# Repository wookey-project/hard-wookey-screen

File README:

# WooKey Screen PCB

## Introduction

Wookey | https://wookey-project.github.io/
Copyright 2018 The wookey project team <wookey@ssi.gouv.fr>

The Wookey from [ANSSI](https://www.ssi.gouv.fr) is an open source
hardware design, implementing an Encrypted Flash Drives.

This repository is aimed towards developers.

### Revision information

This directory contains the hardware design for the Wookey board, first public version (Wookey V2).

### PCB editing tools

All PCB files (schematic and PCB layout) have been designed using the KiCad EDA.
This Cross Platform and Open Source Electronics Design Automation Suite can be downloaded
on http://kicad-pcb.org/.

## Production files generation 101

### Configure the project

KiCad binaries location may change regarding your operating system.
This is why you have to set your environment.
This is done by sourcing the `setenv.sh` script. This script exports
all paths that are required in order to automaticaly generate the production files.

Most of the time, the paths proposed in this script are not the one you use in your specific installation.
The `setenv.sh` script support easy variables overloading by including a `setenv.local.sh` script file if this file exists in the same directory.
If you need to overload some of the variables of the `setenv.sh` script, just add them to your own `setenv.local.sh` file.
Here is an example to define KiCad environement path on Apple Mac OS.

```
  $ echo "export PYTHON_BIN_PATH = /Applications/KiCad/kicad.app/Contents/Frameworks/Python.framework/Versions/2.7/bin/python" > setenv.local.sh
  $ source setenv.sh
  Loading local SDK settings...
  =========================================================
  === Kicad environment configuration
  =========================================================
  PYTHON_BIN_PATH   = /Applications/KiCad/kicad.app/Contents/Frameworks/Python.framework/Versions/2.7/bin/python
  PYTHON_PATH     = /Applications/Kicad/kicad.app/Contents/Frameworks/python/site-packages
  BOM_GEN_PATH = /Applications/Kicad/kicad.app/Contents/SharedSupport/plugins/bom2grouped_csv.xsl
  TOOLS_PATH = ../../../tools
  =========================================================
```

The production files can be generated using the following command.

```
$ make
```

This will generate the production files in a new sub directory.
The directory name may differ according the project your are working with.

## PCB Pinout

## PCB Layers

### PCB TOP layer

### PCB BOTTOM layer

### Layers

Order and type of copper layers:
  TOP:  signal, front components
  GND:  ground plane
  PWR:  ground and power plane
  BOT:  signal, back components

### Stackup
4 layers, 1.6mm thickness
Outer layers 1 oz base copper foil
Inner layers 0.5 oz base copper foil

Electroless Nickel Immersion Gold (ENIG) surface finish

solder resist   0.0254mm
copper          0.0356mm    L1 (TOP)
FR408 prepreg   0.1702mm
copper          0.0178mm    L2 (GND)
FR408           1.1938mm
copper          0.0178mm    L3 (PWR)
FR408 prepreg   0.1702mm
copper          0.0356mm    L4 (BOT)
solder resist   0.0254mm

The substrate for both the core and prepreg is FR408,
with a dielectric constant of 3.66 at 1GHz.
The prepreg is comprised of 2 layers of Isola 2113.

## Regulatory compliance & handling

The Wookey board is intended for use as a development platform for hardware
or software. The board is an open system design, which does not include a
shielded enclosure. This may cause interference to other electrical or
electronic devices in close proximity. In a domestic environment, this product
may cause radio interference in which case the user may be required to take
adequate measures. In addition, this board should not be used near any medical
equipment or RF devices.

The board is sensitive to ESD. Hold the board only by its edges. After removing
the board from its box, place it on a grounded, static-free surface.

The board can become hot, like any fan-less design, during continuous high CPU
loads, mind its temperature while handling it.

## License

Wookey | https://wookey-project.github.io/
Copyright 2018 The wookey project team <wookey@ssi.gouv.fr>

This is an open hardware design licensed under the terms of the CERN Open
Hardware Licence (OHL) v1.2.

You may redistribute and modify this documentation under the terms of the CERN
OHL v.1.2 (http://ohwr.org/cernohl). This documentation is distributed WITHOUT
ANY EXPRESS OR IMPLIED WARRANTY, INCLUDING OF MERCHANTABILITY, SATISFACTORY
QUALITY AND FITNESS FOR A PARTICULAR PURPOSE. Please see the CERN OHL v.1.2 for
applicable conditions.

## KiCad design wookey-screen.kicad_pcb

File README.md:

# WooKey Screen PCB

## Introduction

Wookey | https://wookey-project.github.io/
Copyright 2018 ANSSI

Authors: The Wookey project Team <wookey@ssi.gouv.fr>

The Wookey from [ANSSI](https://www.ssi.gouv.fr) is an open source
hardware design, implementing an Encrypted Flash Drives.

This repository is aimed towards developers.

### Revision information

This directory contains the hardware design for the Wookey board, first public version (Wookey V2).

### PCB editing tools

All PCB files (schematic and PCB layout) have been designed using the KiCad EDA.
This Cross Platform and Open Source Electronics Design Automation Suite can be downloaded
on http://kicad.org/.

## Production files generation 101

### Configure the project

KiCad binaries location may change regarding your operating system.
This is why you have to set your environment.
This is done by sourcing the `setenv.sh` script. This script exports
all paths that are required in order to automaticaly generate the production files.

Most of the time, the paths proposed in this script are not the one you use in your specific installation.
The `setenv.sh` script support easy variables overloading by including a `setenv.local.sh` script file if this file exists in the same directory.
If you need to overload some of the variables of the `setenv.sh` script, just add them to your own `setenv.local.sh` file.
Here is an example to define KiCad environement path on Apple Mac OS.

```
  $ echo "export PYTHON_BIN_PATH = /Applications/KiCad/kicad.app/Contents/Frameworks/Python.framework/Versions/2.7/bin/python" > setenv.local.sh
  $ source setenv.sh
  Loading local SDK settings...
  =========================================================
  === Kicad environment configuration
  =========================================================
  PYTHON_BIN_PATH   = /Applications/KiCad/kicad.app/Contents/Frameworks/Python.framework/Versions/2.7/bin/python
  PYTHON_PATH     = /Applications/Kicad/kicad.app/Contents/Frameworks/python/site-packages
  BOM_GEN_PATH = /Applications/Kicad/kicad.app/Contents/SharedSupport/plugins/bom2grouped_csv.xsl
  TOOLS_PATH = ../../../tools
  =========================================================
```

The production files can be generated using the following command.

```
$ make
```

This will generate the production files in a new sub directory.
The directory name may differ according the project your are working with.

## PCB Pinout

## PCB Layers

### PCB TOP layer

### PCB BOTTOM layer

### Layers

Order and type of copper layers:
  TOP:  signal, front components
  GND:  ground plane
  PWR:  ground and power plane
  BOT:  signal, back components

### Stackup
4 layers, 1.6mm thickness
Outer layers 1 oz base copper foil
Inner layers 0.5 oz base copper foil

Electroless Nickel Immersion Gold (ENIG) surface finish

solder resist   0.0254mm
copper          0.0356mm    L1 (TOP)
FR408 prepreg   0.1702mm
copper          0.0178mm    L2 (GND)
FR408           1.1938mm
copper          0.0178mm    L3 (PWR)
FR408 prepreg   0.1702mm
copper          0.0356mm    L4 (BOT)
solder resist   0.0254mm

The substrate for both the core and prepreg is FR408,
with a dielectric constant of 3.66 at 1GHz.
The prepreg is comprised of 2 layers of Isola 2113.

## Regulatory compliance & handling

The Wookey board is intended for use as a development platform for hardware
or software. The board is an open system design, which does not include a
shielded enclosure. This may cause interference to other electrical or
electronic devices in close proximity. In a domestic environment, this product
may cause radio interference in which case the user may be required to take
adequate measures. In addition, this board should not be used near any medical
equipment or RF devices.

The board is sensitive to ESD. Hold the board only by its edges. After removing
the board from its box, place it on a grounded, static-free surface.

The board can become hot, like any fan-less design, during continuous high CPU
loads, mind its temperature while handling it.

## License

Wookey | https://wookey-project.github.io/

Copyright 2019 ANSSI

Authors: The Wookey project Team <wookey@ssi.gouv.fr>

This is an open hardware design licensed under the terms of the CERN Open
Hardware Licence (OHL) v1.2.

You may redistribute and modify this documentation under the terms of the CERN
OHL v.1.2 (http://ohwr.org/cernohl). This documentation is distributed WITHOUT
ANY EXPRESS OR IMPLIED WARRANTY, INCLUDING OF MERCHANTABILITY, SATISFACTORY
QUALITY AND FITNESS FOR A PARTICULAR PURPOSE. Please see the CERN OHL v.1.2 for
applicable conditions.

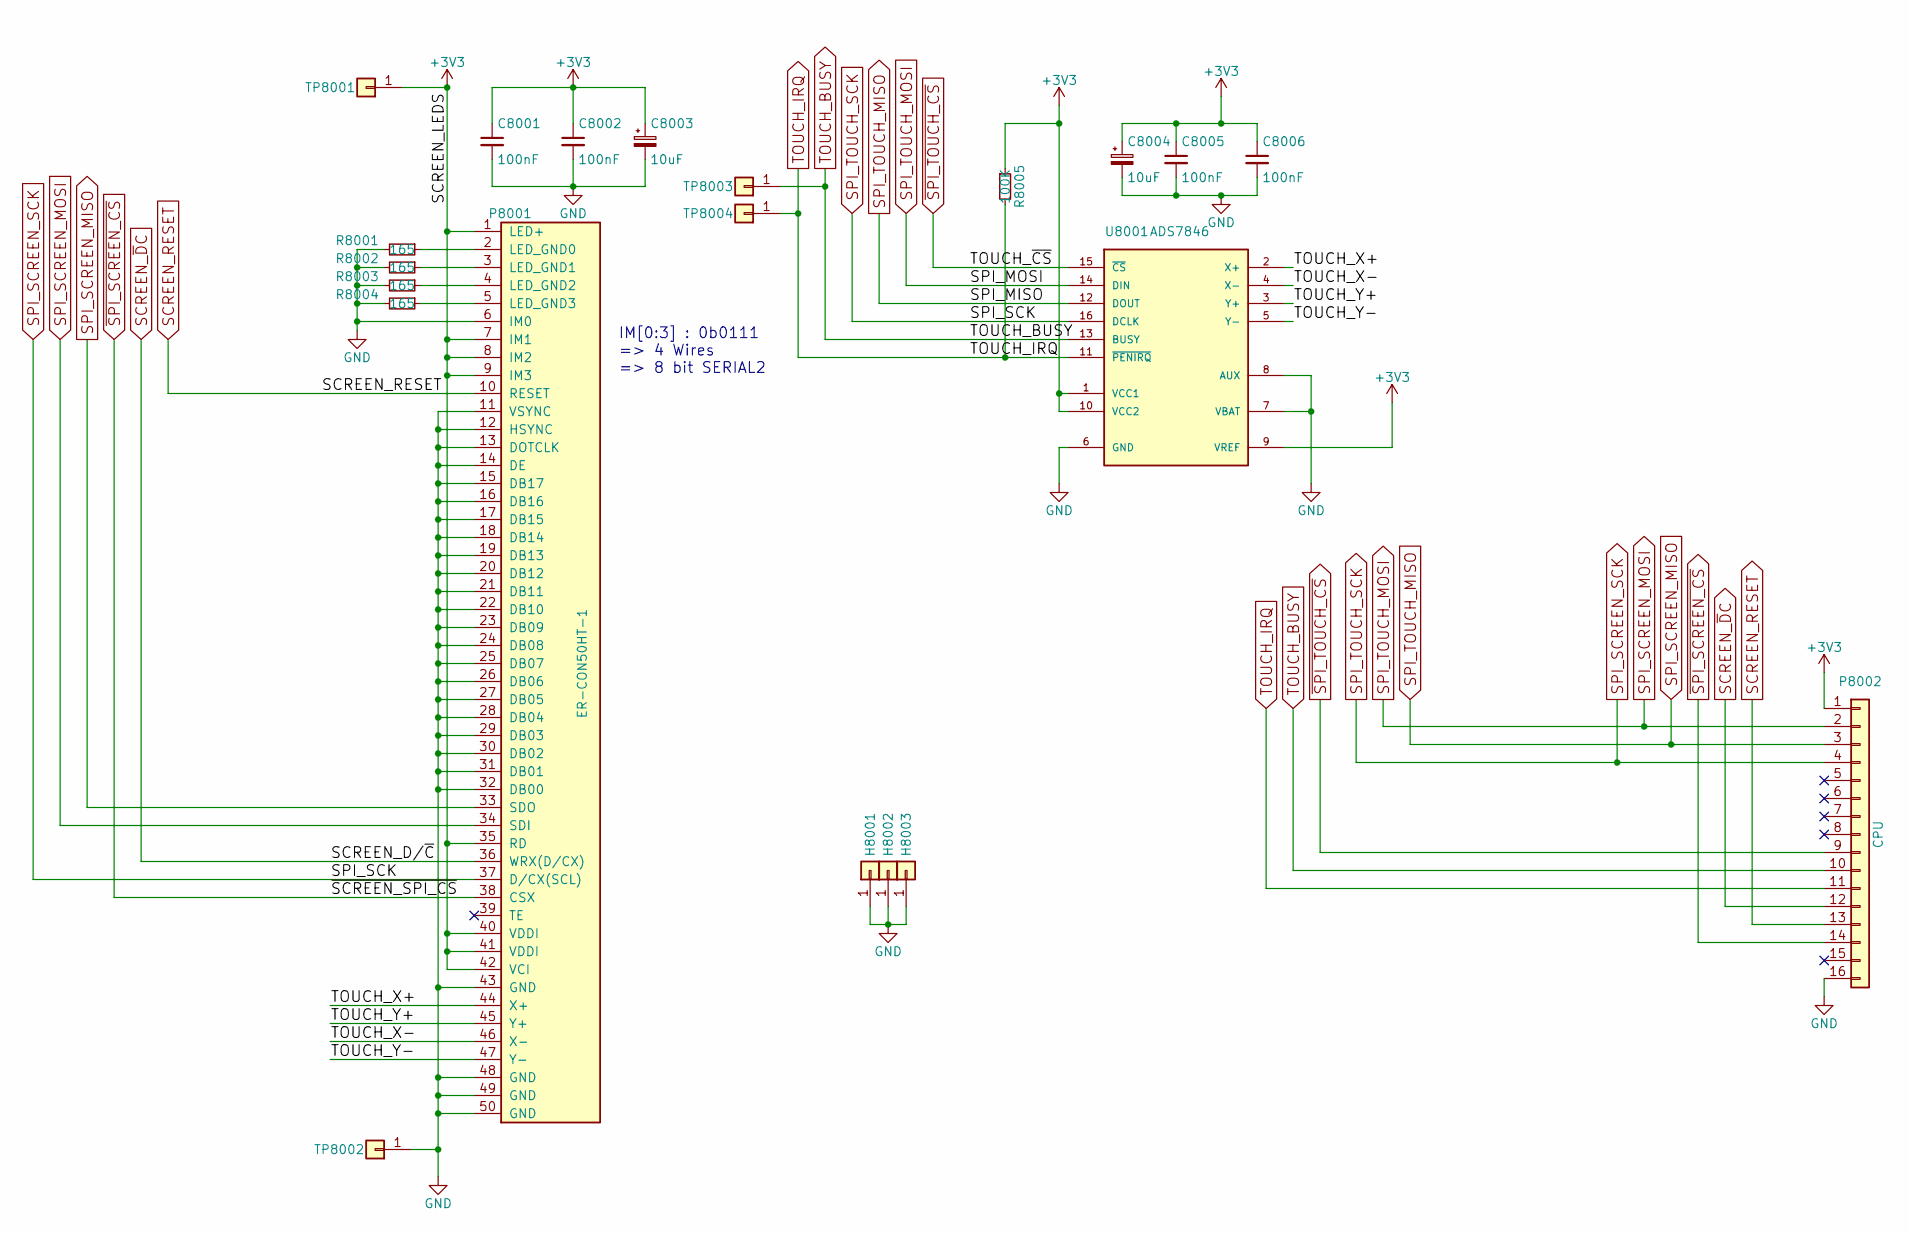
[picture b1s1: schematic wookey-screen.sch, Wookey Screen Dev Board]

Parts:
C8001, C8002, C8005, C8006: 100nF; C_0603_1608Metric; MFG Part Num 0603YC104JAT2A
C8003, C8004: 10uF; CP_EIA-1608-08_AVX-J; MFG Part Num TP8M106M6R3C
H8001: H1; MountingHole_2.2mm_M2_ISO14580_Pad
H8002, H8003: H2; MountingHole_2.2mm_M2_ISO14580_Pad
P8001: ER-CON50HT-1; BuyDisplay-50PIN_LCD_ZIF; MFG Part Num 541045096
P8002: CPU; FPC16_MOLEX_52892_1633; MFG Part Num 52892-1633
R8001, R8002, R8003, R8004: 165; R_0603_1608Metric; MFG Part Num ERJ3EKF1650V
R8005: 100K; R_0603_1608Metric; MFG Part Num 2059655
TP8001, TP8002, TP8004: TP901; TestPoint_Pad_2.0x2.0mm
TP8003: TP902; TestPoint_Pad_2.0x2.0mm
U8001: ADS7846; SSOP-16_3.9x4.9mm_P0.635mm; MFG Part Num ADS7846E

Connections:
+3V3: C8001.1, C8002.1, C8003.1, C8004.1, C8005.1, C8006.1, P8001.1 (LED+), P8001.7 (IM1), P8001.8 (IM2), P8001.9 (IM3), P8001.35 (RD), P8001.40 (VDDI), P8001.41 (VDDI), P8001.42 (VCI), P8002.1, R8005.1, TP8001.1, U8001.1 (VCC1), U8001.9 (VREF), U8001.10 (VCC2)
/TOUCH_X+: P8001.44 (X+), U8001.2 (X+)
/TOUCH_X-: P8001.46 (X-), U8001.4 (X-)
/TOUCH_Y+: P8001.45 (Y+), U8001.3 (Y+)
/TOUCH_Y-: P8001.47 (Y-), U8001.5 (Y-)
GND: C8001.2, C8002.2, C8003.2, C8004.2, C8005.2, C8006.2, H8001.1, H8002.1, H8003.1, P8001.6 (IM0), P8001.11 (VSYNC), P8001.12 (HSYNC), P8001.13 (DOTCLK), P8001.14 (DE), P8001.15 (DB17), P8001.16 (DB16), P8001.17 (DB15), P8001.18 (DB14), P8001.19 (DB13), P8001.20 (DB12), P8001.21 (DB11), P8001.22 (DB10), P8001.23 (DB09), P8001.24 (DB08), P8001.25 (DB07), P8001.26 (DB06), P8001.27 (DB05), P8001.28 (DB04), P8001.29 (DB03), P8001.30 (DB02), P8001.31 (DB01), P8001.32 (DB00), P8001.43 (GND), P8001.48 (GND), P8001.49 (GND), P8001.50 (GND), P8002.16, R8001.2, R8002.2, R8003.2, R8004.2, TP8002.1, U8001.6 (GND), U8001.7 (VBAT), U8001.8 (AUX)
unnamed: P8001.2 (LED_GND0), R8001.1
unnamed: P8001.3 (LED_GND1), R8002.1
unnamed: P8001.4 (LED_GND2), R8003.1
unnamed: P8001.5 (LED_GND3), R8004.1
SCREEN_RESET: P8001.10 (RESET), P8002.13
SCREEN_~D~C: P8001.36 (WRX(D/CX)), P8002.12
SPI_SCREEN_MISO: P8001.33 (SDO), P8002.3, U8001.12 (DOUT)
SPI_SCREEN_MOSI: P8001.34 (SDI), P8002.2, U8001.14 (DIN)
SPI_SCREEN_SCK: P8001.37 (D/CX(SCL)), P8002.4, U8001.16 (DCLK)
TOUCH_BUSY: P8002.10, TP8003.1, U8001.13 (BUSY)
TOUCH_IRQ: P8002.11, R8005.2, TP8004.1, U8001.11 (~PENIRQ)
~SPI_SCREEN_CS: P8001.38 (CSX), P8002.14
~SPI_TOUCH_CS: P8002.9, U8001.15 (~CS)

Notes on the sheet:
IM[0:3] : 0b0111 => 4 Wires => 8 bit SERIAL2

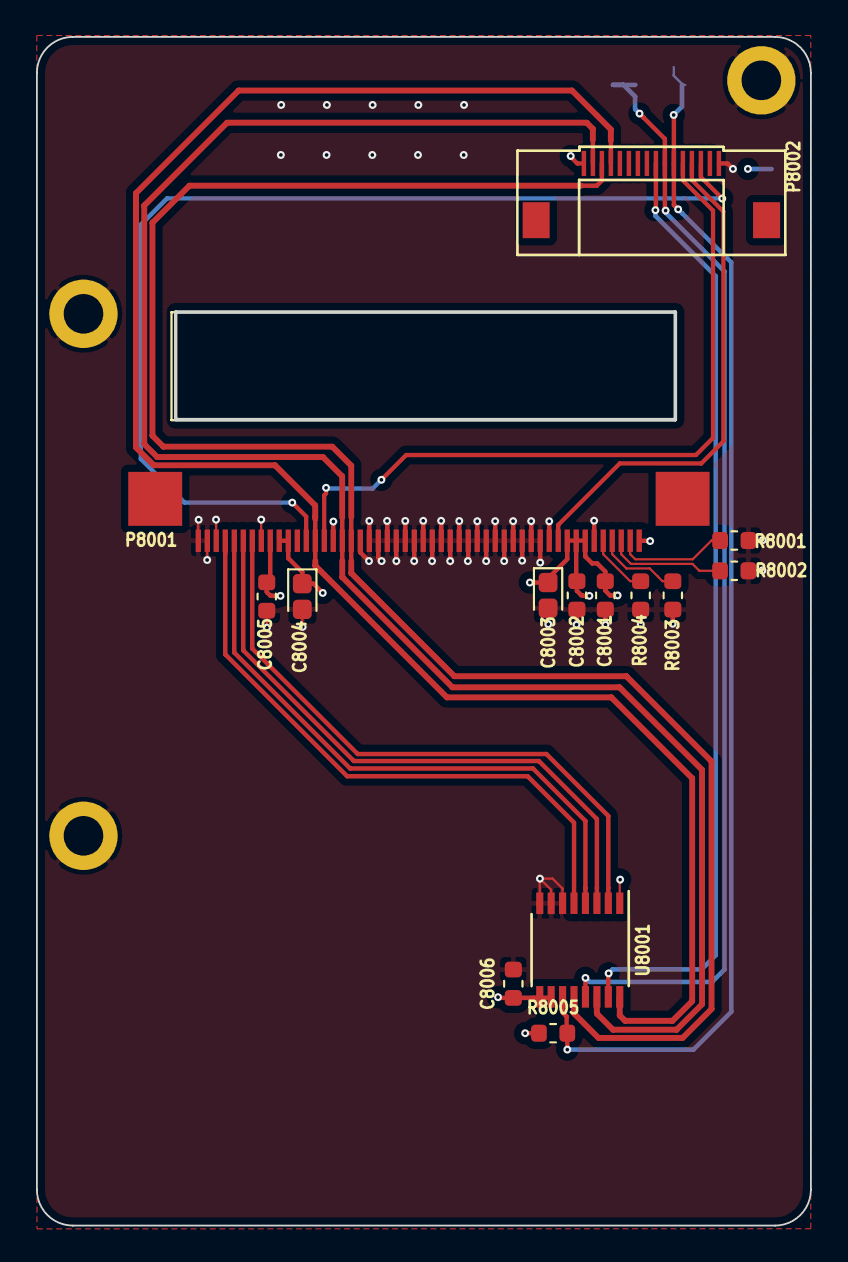
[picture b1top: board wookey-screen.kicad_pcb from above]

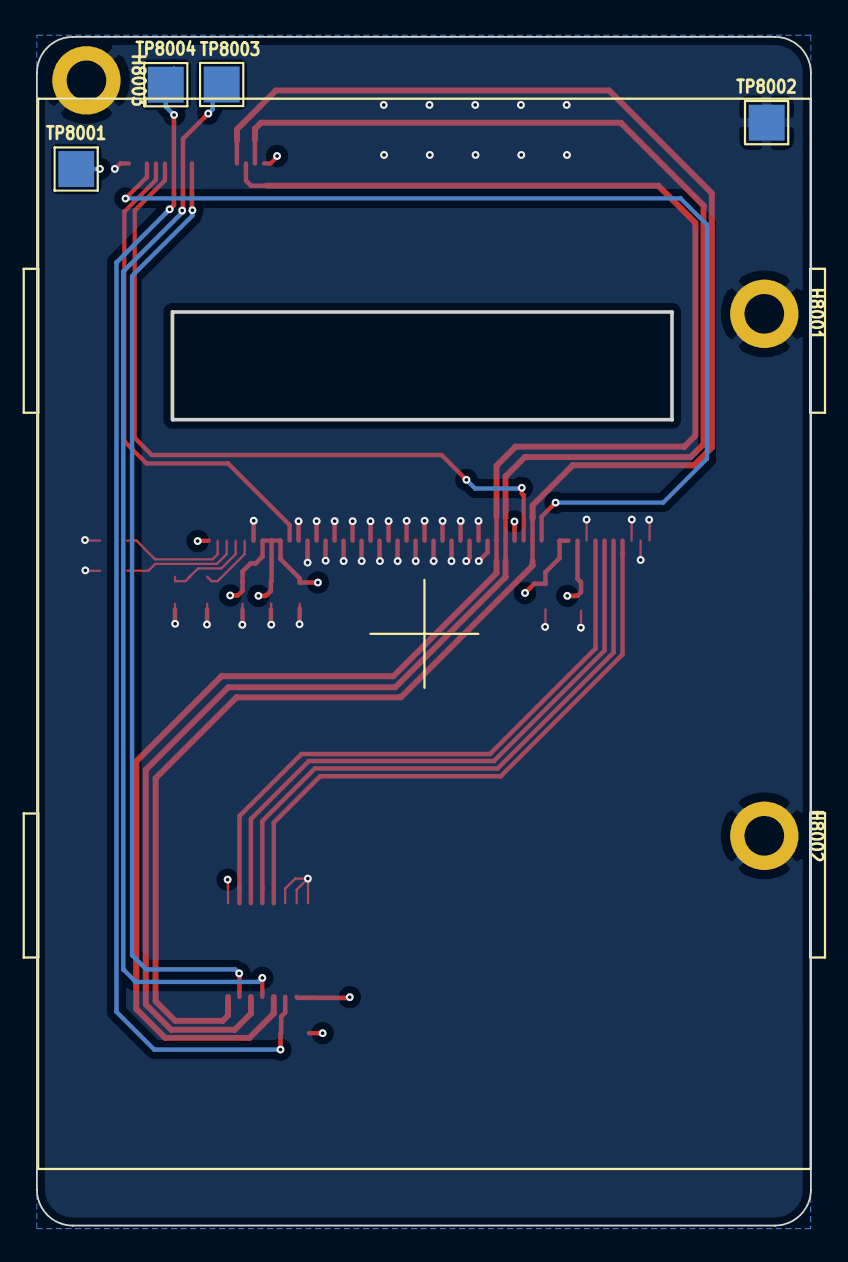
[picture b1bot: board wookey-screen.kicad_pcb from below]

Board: 4 copper layers, 42.9 x 65.9 mm, 21 parts (8 on the bottom side), 19 nets.

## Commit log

2019-05-15 First import
2019-05-16 [enhancement] : add debian sample configuration file
2019-05-17 [enhancement] Update README and imgs
2019-05-17 [enhancement] Reference LICENSE in files
2019-05-17 [enhancement] global cleanup
2019-05-17 [enhancement] Add README and imgs files
2019-05-17 [enhancement] Add LICENSE.txt
2019-05-17 [enhancement] General cleanup
2019-05-17 [enhancement] add pcb screenshots
2019-05-17 [enhancement] move pcb screenshots to imgs directory
2019-05-17 [enhancement] Add setenv.local examples
2019-05-17 [fix] Rename files.
2019-08-26 [bugfix] copyright typo
2021-11-08 Update README.md
    https://forum.kicad.info/t/warning-avoid-all-links-to-kicad-pcb-org-use-kicad-org/31521

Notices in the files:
wookey-screen.sch:
LICENCE: CERN Open Hardware Licence v1.2
